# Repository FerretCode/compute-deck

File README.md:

# Compute Deck

**Compute Deck** is an open-source portable Linux computer and cyberdeck platform. It features a BlackBerry Q10 physical keyboard, dedicated power management with LiPo charging, an RP2040 coprocessor serving as an I2C keyboard bridge, and a Linux compute module.

> [!WARNING]
> ### ⚠️ Hardware Revision Notice: RK3566 Migration In Progress
>
> Revisions 1 and 2 of this project were built and verified around a **Raspberry Pi Zero / Zero 2 W** form-factor header.
>
> The project is currently undergoing a major hardware architecture update to migrate from the Pi Zero header to an integrated Rockchip RK3566 SoC directly on the board.
---

## Project Overview & Key Features

- **Physical Keyboard Integration:** Uses a BlackBerry Q10 keyboard connected using a 24-pin Hirose BM14B connector.
- **Dedicated RP2040 Coprocessor:** Offloads the keyboard control from the processor, supporting debouncing, key remapping, and layer management.
- **I2C Slave Keyboard Bridge:** Communicates with the host system via I2C at address `0x1F`, sending keycodes to the main processor.
- **Power Management Subsystem:** Integrated IP5306 power bank SoC managing single-cell LiPo battery charging, 5V boost conversion, power routing, status LEDs, and soft-latching power control alongside an AMS1117-3.3 regulator.
- **Linux Host Virtual Keyboard Driver:** Python user-space daemon using Linux `/dev/uinput` and `evdev` to translate the RP2040 I2C keycodes into full USB keyboard input with support for modifiers.

---

## Repository Structure

```
compute-deck/
├── firmware/                   # RP2040 Coprocessor Firmware (Pico SDK C/C++)
│   ├── CMakeLists.txt          # CMake build configuration
│   ├── main.c                  # Keyboard matrix scanner, layer logic & I2C slave handler
├── hardware/                   # KiCad PCB & Schematic Design Files
│   ├── footprints/             # Custom KiCad component footprints
│   ├── symbols/                # Custom KiCad schematic symbols
├── host/                       # Host Linux Software & Services
│   ├── keyboard_driver.py      # Python I2C polling daemon & uinput event injector
│   ├── q10-keyboard.service    # Systemd service unit for boot startup
```

---

## RP2040 Firmware Setup

### Build Prerequisites

- [Raspberry Pi Pico SDK](https://github.com/raspberrypi/pico-sdk) configured in your environment (`PICO_SDK_PATH`).
- `cmake`
- GCC ARM Cross-compiler (`arm-none-eabi-gcc`)

### Building the Firmware

```bash
cd firmware
mkdir build
cd build
cmake ..
make -j$(nproc)
```

### Flashing

1. Short the `BOOTSEL` jumper on the board using tweezers or other conductive object while plugging in USB to enter the RP2040 into bootloader mode.
2. Drag and drop `q10_keyboard.uf2` onto the mounted `RPI-RP2` USB storage drive.

---

## Host Driver Setup (Linux / Raspberry Pi OS)

The host driver in `host/` runs on the Linux compute host (e.g. Raspberry Pi OS or Linux kernel with `/dev/uinput` enabled).

### 1. Enable I2C Interface
Enable the hardware I2C interface on the host SBC:

```bash
sudo raspi-config nonint do_i2c 0
```

### 2. Install Dependencies
```bash
sudo apt-get install python3-pip python3-smbus
pip3 install -r host/requirements.txt
```

### 3. Grant Permissions

Add your user to the `i2c` and `input` groups:

```bash
sudo usermod -aG i2c,input $USER
```

### 4. Running the Driver

Run the driver manually to verify key injection:

```bash
python3 host/keyboard_driver.py
```

### 5. Install as a Systemd Daemon

To launch the keyboard driver automatically at boot:

```bash
sudo mkdir -p /opt/q10-keyboard
sudo cp host/keyboard_driver.py /opt/q10-keyboard/
sudo cp host/q10-keyboard.service /etc/systemd/system/
sudo systemctl daemon-reload
sudo systemctl enable --now q10-keyboard.service
```

---

## Keyboard Layout & Modifier Behavior

The physical layout follows the BlackBerry Q10 matrix mapping:

- **Shift:** One-shot modifier. Pressing Shift capitalizes the next key typed, and then automatically clears.
- **Alt:** Accesses numbers and secondary symbols printed on keycaps (e.g., Q -> `#`, W -> `1`, E -> `2`).
- **Sym:** Accesses extended navigation and punctuation symbols (e.g., Q -> `Esc`, W -> `Up`, A -> `Left`, S -> `Down`, D -> `Right`, T -> `Tab`).
- **Mic Key:** Mapped as Super. Supports tap-or-chord timeout (`0.4s`).
- **Ctrl:** Left Control key with chord support.

---

## Fabrication & Manufacturing

Production files generated for JLCPCB are stored under `hardware/production/`

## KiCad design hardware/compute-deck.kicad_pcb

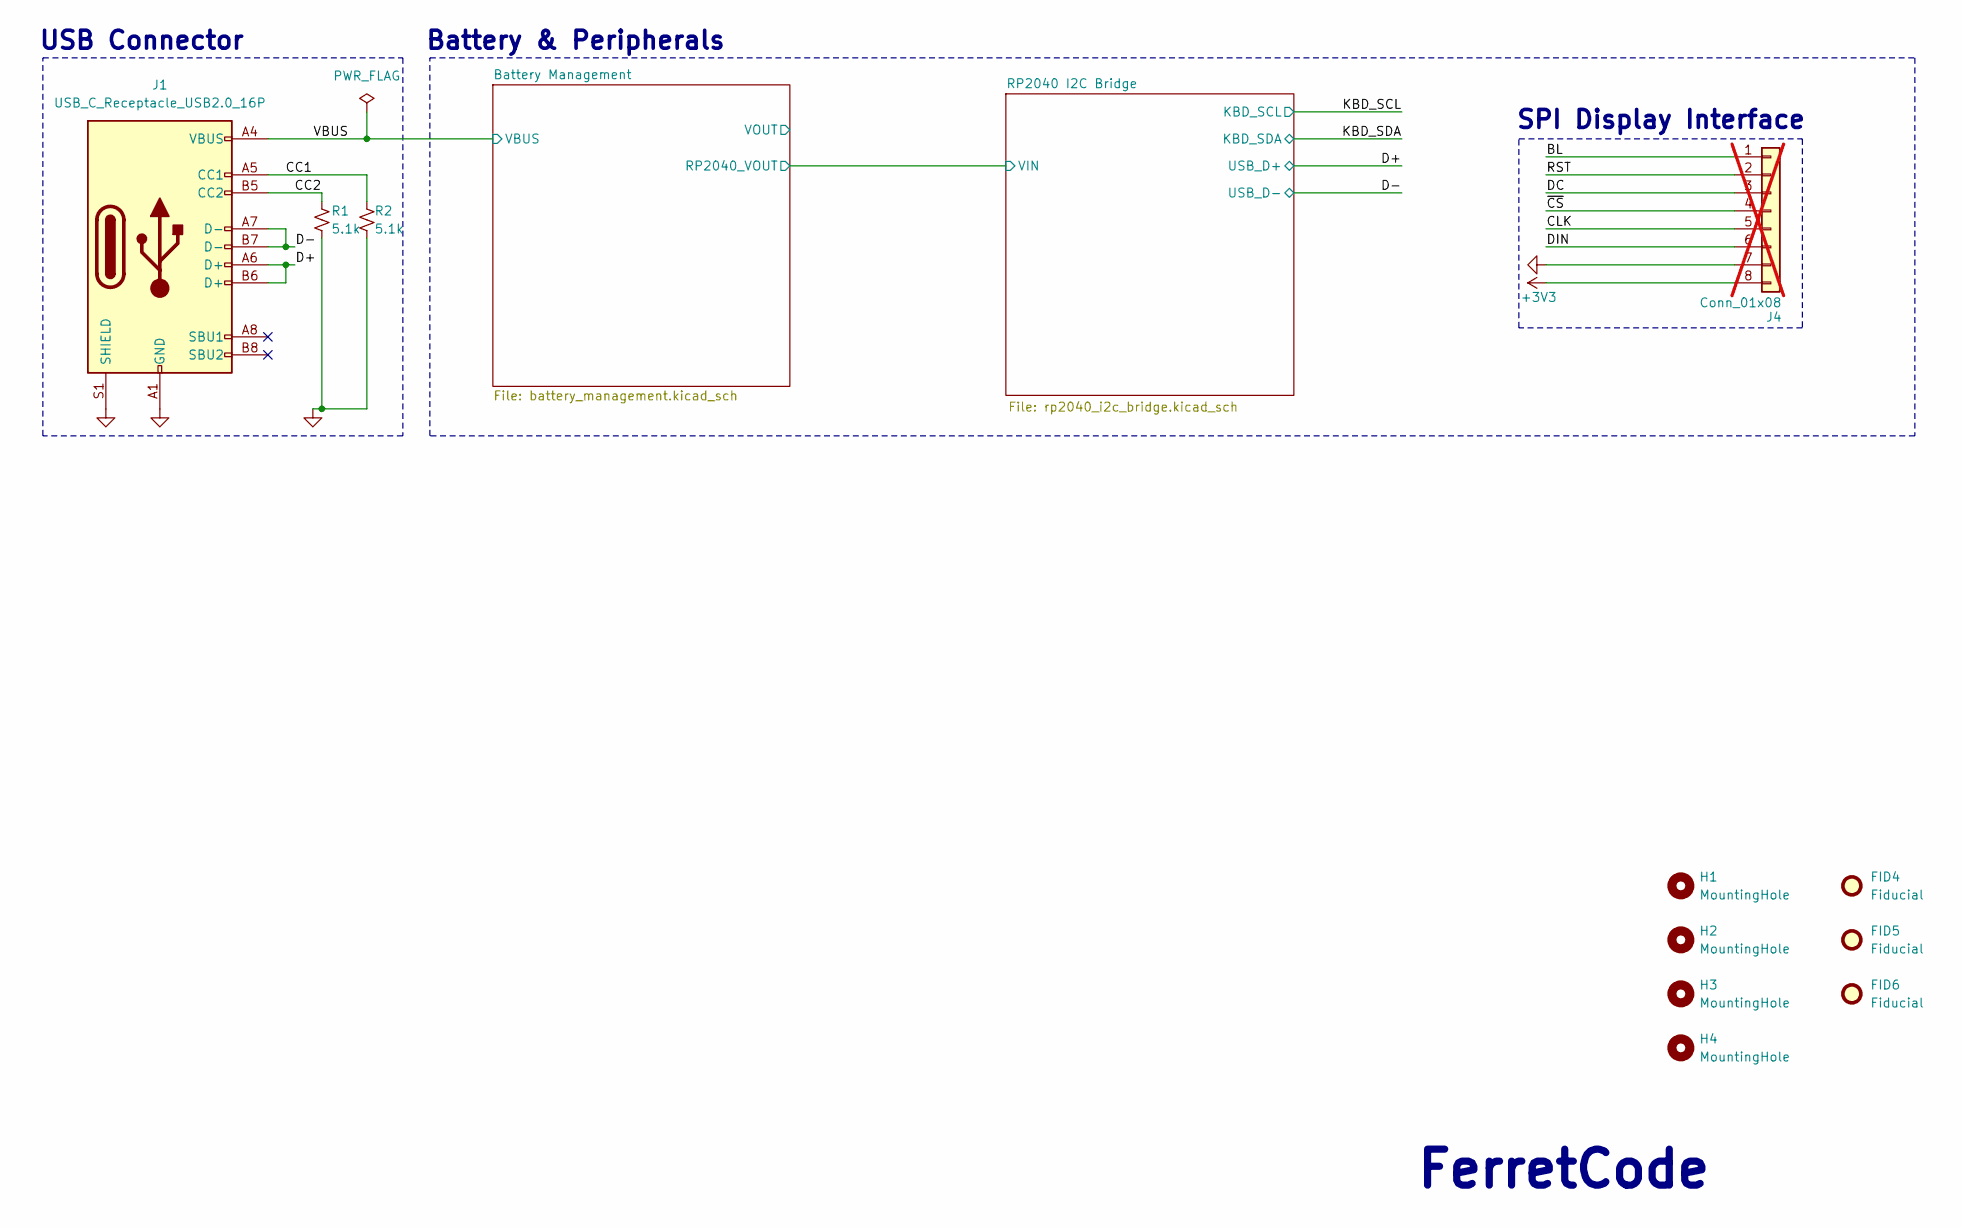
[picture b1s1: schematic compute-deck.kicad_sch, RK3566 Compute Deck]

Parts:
FID4, FID5, FID6: Fiducial; Fiducial_1mm_Mask3mm
H1, H2, H3, H4: MountingHole; MountingHole_2.7mm_M2.5
J1: USB_C_Receptacle_USB2.0_16P; USB_C_Receptacle_HRO_TYPE-C-31-M-12; LCSC PN C165948
J4: Conn_01x08; PinHeader_1x08_P2.54mm_Vertical; not fitted
R1, R2: 5.1k; R_0402_1005Metric; LCSC PN C23186

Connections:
+3V3: J4.8; also elsewhere on the board
/BL: J4.1; also elsewhere on the board
/CC1: J1.A5 (CC1), R2.1
/CC2: J1.B5 (CC2), R1.1
/CLK: J4.5; also elsewhere on the board
/D+: J1.A6 (D+), J1.B6 (D+); also elsewhere on the board
/D-: J1.A7 (D-), J1.B7 (D-); also elsewhere on the board
/DC: J4.3; also elsewhere on the board
/DIN: J4.6; also elsewhere on the board
/RST: J4.2; also elsewhere on the board
/VBUS: J1.A4 (VBUS), J1.A9 (VBUS), J1.B4 (VBUS), J1.B9 (VBUS); also elsewhere on the board
/~CS: J4.4; also elsewhere on the board
GND: J1.A1 (GND), J1.A12 (GND), J1.B1 (GND), J1.B12 (GND), J1.S1 (SHIELD), J4.7, R1.2, R2.2; also elsewhere on the board

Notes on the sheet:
Battery & Peripherals
FerretCode
SPI Display Interface
USB Connector

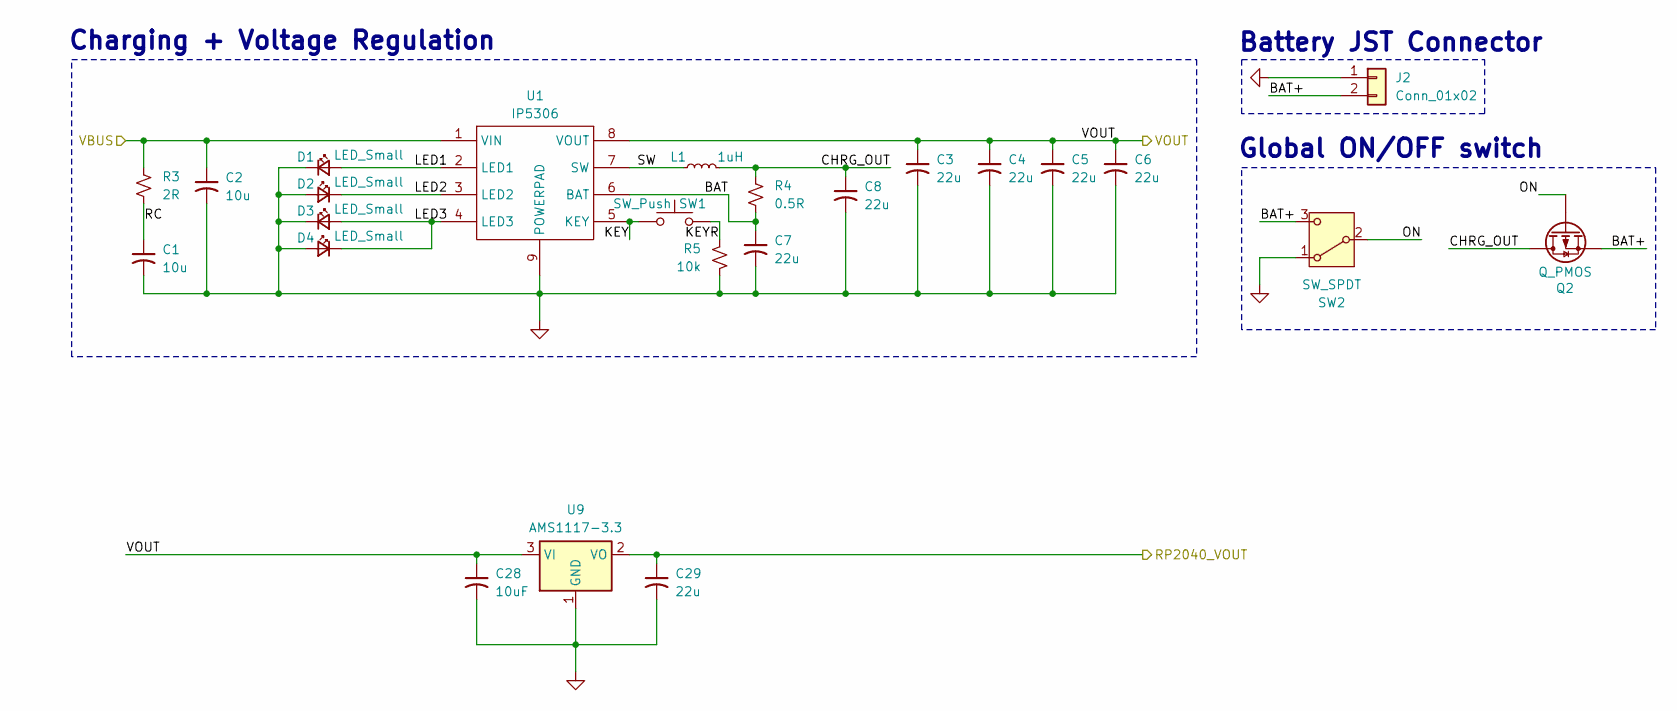
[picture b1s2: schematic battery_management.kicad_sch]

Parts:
C1, C2: 10u; C_0603_1608Metric; LCSC PN C19702
C3, C4, C5, C6: 22u; C_0805_2012Metric; LCSC PN C29277
C7: 22u; C_0402_1005Metric; LCSC PN C60077
C8: 22u; C_0603_1608Metric; LCSC PN C60077
C28: 10uF; C_0603_1608Metric; LCSC C19702
C29: 22u; C_0603_1608Metric; LCSC C59461
D1, D2, D3, D4: LED_Small; LED_0603_1608Metric; LCSC PN C6695603
J2: Conn_01x02; JST_PH_S2B-PH-K_1x02_P2.00mm_Horizontal; LCSC PN C157932
L1: 1uH; L_Taiyo-Yuden_NR-60xx; LCSC PN C2903082
Q2: Q_PMOS; SOT-23
R3: 2R; R_0603_1608Metric; LCSC PN C22977
R4: 0.5R; R_0402_1005Metric; LCSC PN C45312
R5: 10k; R_0402_1005Metric; LCSC PN C25804
SW1: SW_Push; SW_Push_1P1T_NO_CK_KMR2; LCSC PN C221675
SW2: SW_SPDT; SW_SPDT_PCM12
U1: IP5306; SOP127P600X165-9N
U9: AMS1117-3.3; SOT-223-3_TabPin2; LCSC C6186

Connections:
/BAT: C7.1, R4.2, U1.6 (BAT)
/BAT+: J2.2, Q2.S, SW2.3 (C)
/CHRG_OUT: C8.1, L1.2, Q2.D, R4.1
/KEY: SW1.1, U1.5 (KEY)
/KEYR: R5.1, SW1.2
/LED1: D1.2 (A), U1.2 (LED1)
/LED2: D2.1 (K), U1.3 (LED2)
/LED3: D3.2 (A), D4.1 (K), U1.4 (LED3)
/ON: Q2.G, SW2.2 (B)
/RC: C1.1, R3.2
/SW: L1.1, U1.7 (SW)
/VBUS: C2.1, R3.1, U1.1 (VIN); also elsewhere on the board
/VOUT: C3.1, C4.1, C5.1, C6.1, C28.1, U1.8 (VOUT), U9.3 (VI); also elsewhere on the board
GND: C1.2, C2.2, C3.2, C4.2, C5.2, C6.2, C7.2, C8.2, C28.2, C29.2, D1.1 (K), D2.2 (A), D3.1 (K), D4.2 (A), J2.1, R5.2, SW2.1 (A), U1.9 (POWERPAD), U9.1 (GND); also elsewhere on the board
unnamed: C29.1, U9.2 (VO)

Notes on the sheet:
Charging + Voltage Regulation
Global ON/OFF switch
Battery JST Connector

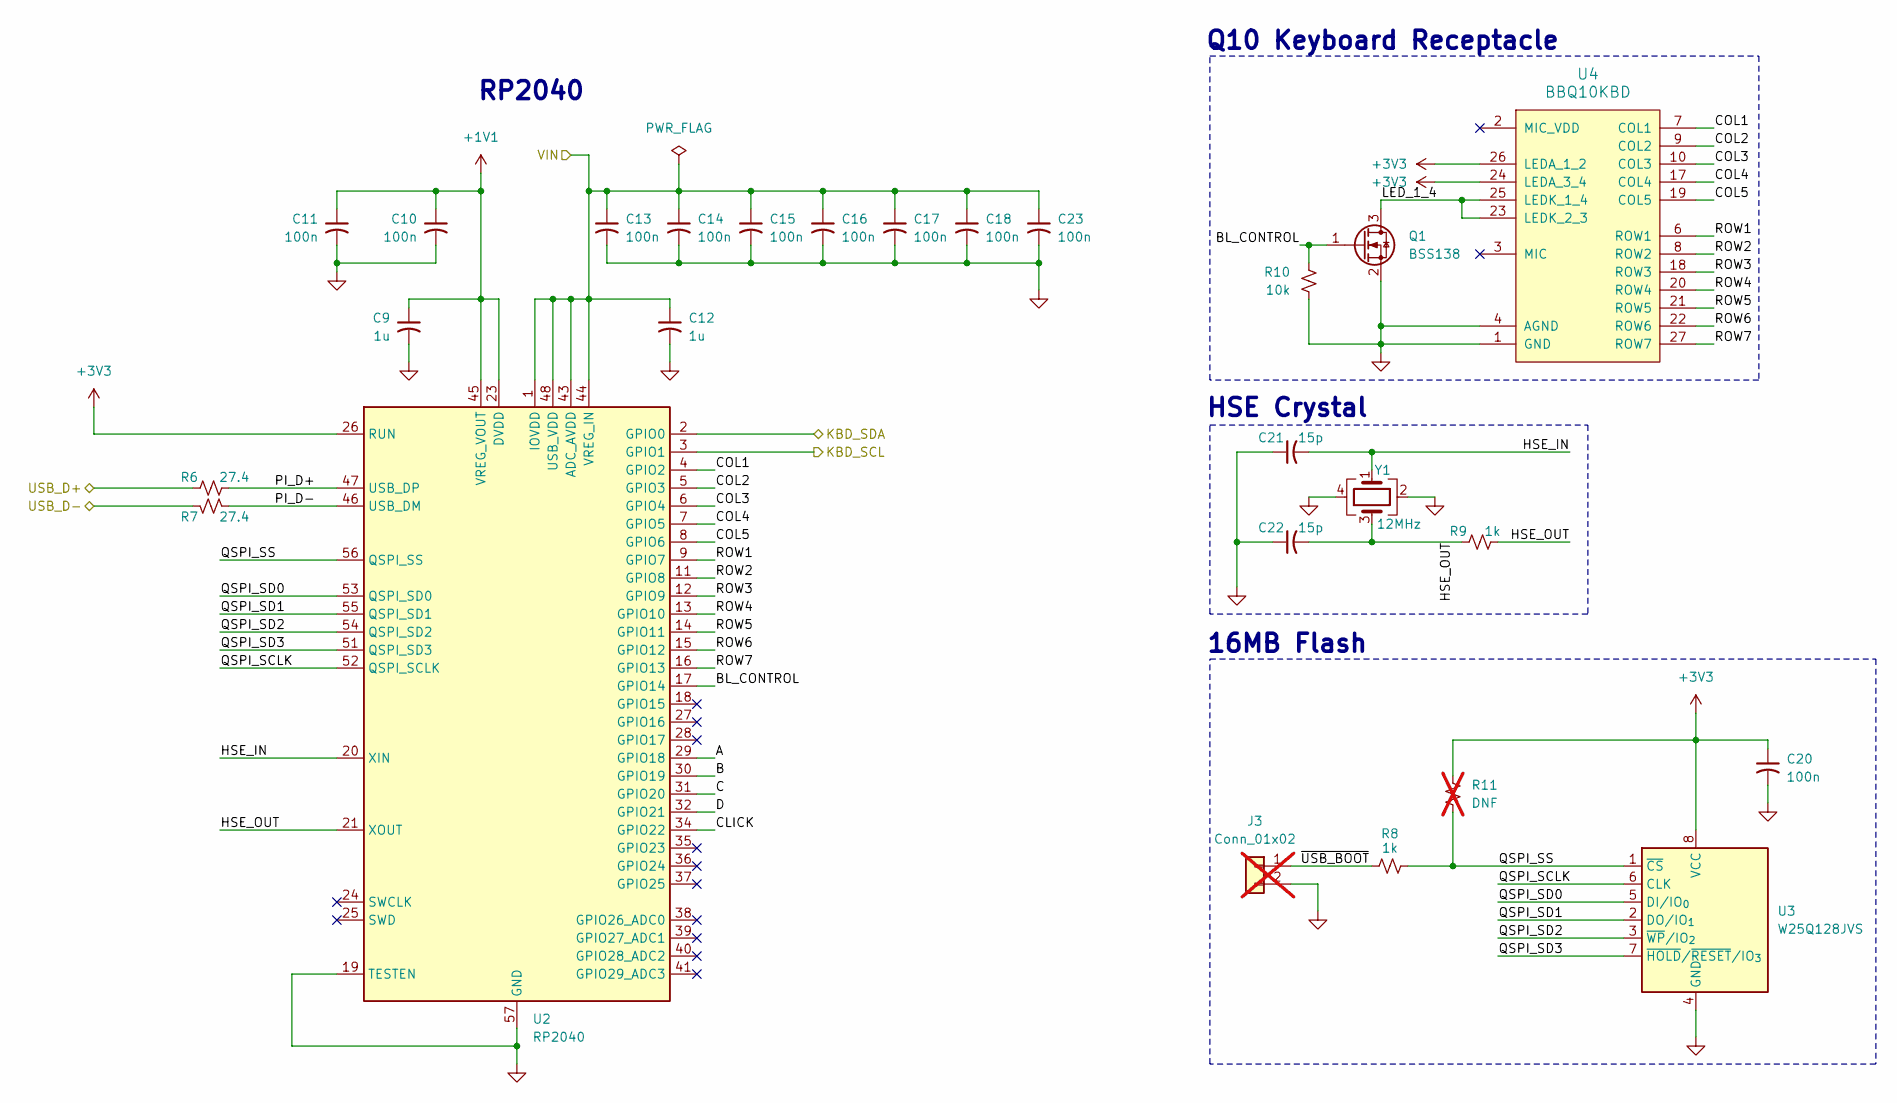
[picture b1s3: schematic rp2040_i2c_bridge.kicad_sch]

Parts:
C9: 1u; C_0402_1005Metric; LCSC PN C14445
C10, C11, C13, C14, C16, C17, C18: 100n; C_0402_1005Metric; LCSC PN C71687
C12: 1u; C_0603_1608Metric; LCSC PN C14445
C15: 100n; C_0402_1005Metric
C20: 100n; C_0603_1608Metric; LCSC PN C1590
C21, C22: 15p; C_0402_1005Metric; LCSC PN C1548
C23: 100n; C_0402_1005Metric_Pad0.74x0.62mm_HandSolder; LCSC PN C71687
J3: Conn_01x02; PinHeader_1x02_P2.54mm_Vertical; not fitted
Q1: BSS138; SOT-23; LCSC PN C52895
R6, R7: 27.4; R_0402_1005Metric; LCSC PN C177713
R8, R9: 1k; R_0402_1005Metric; LCSC PN C21190
R10: 10k; R_0603_1608Metric; LCSC PN C25804
R11: DNF; R_0402_1005Metric; not fitted
U2: RP2040; QFN-56-1EP_7x7mm_P0.4mm_EP3.2x3.2mm; LCSC PN C2040
U3: W25Q128JVS; SOIC-8_5.3x5.3mm_P1.27mm
U4: BBQ10KBD; BM14B(0.8)-24DS-0.4V(53)
Y1: 12MHz; Crystal_SMD_3225-4Pin_3.2x2.5mm; LCSC PN C9002

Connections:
+1V1: C9.1, C10.1, C11.1, U2.23 (DVDD), U2.45 (VREG_VOUT), U2.50 (DVDD)
+3V3: C12.1, C13.1, C14.1, C15.1, C16.1, C17.1, C18.1, C20.1, C23.1, R11.1, U2.1 (IOVDD), U2.10 (IOVDD), U2.22 (IOVDD), U2.26 (RUN), U2.33 (IOVDD), U2.42 (IOVDD), U2.43 (ADC_AVDD), U2.44 (VREG_IN), U2.48 (USB_VDD), U2.49 (IOVDD), U3.8 (VCC), U4.24 (LEDA_3_4), U4.26 (LEDA_1_2); also elsewhere on the board
/D+: R6.1; also elsewhere on the board
/D-: R7.1; also elsewhere on the board
/KBD_SCL: U2.3 (GPIO1); also elsewhere on the board
/KBD_SDA: U2.2 (GPIO0); also elsewhere on the board
/RP2040 I2C Bridge/A: U2.29 (GPIO18)
/RP2040 I2C Bridge/B: U2.30 (GPIO19)
/RP2040 I2C Bridge/BL_CONTROL: Q1.1 (G), R10.1, U2.17 (GPIO14)
/RP2040 I2C Bridge/C: U2.31 (GPIO20)
/RP2040 I2C Bridge/CLICK: U2.34 (GPIO22)
/RP2040 I2C Bridge/COL1: U2.4 (GPIO2), U4.7 (COL1)
/RP2040 I2C Bridge/COL2: U2.5 (GPIO3), U4.9 (COL2)
/RP2040 I2C Bridge/COL3: U2.6 (GPIO4), U4.10 (COL3)
/RP2040 I2C Bridge/COL4: U2.7 (GPIO5), U4.17 (COL4)
/RP2040 I2C Bridge/COL5: U2.8 (GPIO6), U4.19 (COL5)
/RP2040 I2C Bridge/D: U2.32 (GPIO21)
/RP2040 I2C Bridge/HSE_IN: C21.2, U2.20 (XIN), Y1.1
/RP2040 I2C Bridge/HSE_OUT: C22.2, R9.1, R9.2, U2.21 (XOUT), Y1.3
/RP2040 I2C Bridge/LED_1_4: Q1.3 (D), U4.23 (LEDK_2_3), U4.25 (LEDK_1_4)
/RP2040 I2C Bridge/PI_D+: R6.2, U2.47 (USB_DP)
/RP2040 I2C Bridge/PI_D-: R7.2, U2.46 (USB_DM)
/RP2040 I2C Bridge/QSPI_SCLK: U2.52 (QSPI_SCLK), U3.6 (CLK)
/RP2040 I2C Bridge/QSPI_SD0: U2.53 (QSPI_SD0), U3.5 (DI/IO_{0})
/RP2040 I2C Bridge/QSPI_SD1: U2.55 (QSPI_SD1), U3.2 (DO/IO_{1})
/RP2040 I2C Bridge/QSPI_SD2: U2.54 (QSPI_SD2), U3.3 (~WP/IO_{2})
/RP2040 I2C Bridge/QSPI_SD3: U2.51 (QSPI_SD3), U3.7 (~HOLD/~RESET/IO_{3})
/RP2040 I2C Bridge/QSPI_SS: R8.2, R11.2, U2.56 (QSPI_SS), U3.1 (~CS)
/RP2040 I2C Bridge/ROW1: U2.9 (GPIO7), U4.6 (ROW1)
/RP2040 I2C Bridge/ROW2: U2.11 (GPIO8), U4.8 (ROW2)
/RP2040 I2C Bridge/ROW3: U2.12 (GPIO9), U4.18 (ROW3)
/RP2040 I2C Bridge/ROW4: U2.13 (GPIO10), U4.20 (ROW4)
/RP2040 I2C Bridge/ROW5: U2.14 (GPIO11), U4.21 (ROW5)
/RP2040 I2C Bridge/ROW6: U2.15 (GPIO12), U4.22 (ROW6)
/RP2040 I2C Bridge/ROW7: U2.16 (GPIO13), U4.27 (ROW7)
/RP2040 I2C Bridge/~USB_BOOT: J3.1, R8.1
GND: C9.2, C10.2, C11.2, C12.2, C13.2, C14.2, C15.2, C16.2, C17.2, C18.2, C20.2, C21.1, C22.1, C23.2, J3.2, Q1.2 (S), R10.2, U2.19 (TESTEN), U2.57 (GND), U3.4 (GND), U4.1 (GND), U4.4 (AGND), U4.5 (GND), U4.11 (GND), U4.12 (GND), U4.13 (GND), U4.14 (GND), U4.15 (GND), U4.16 (GND), U4.28 (GND), Y1.2, Y1.4; also elsewhere on the board

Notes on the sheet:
Q10 Keyboard Receptacle
RP2040
16MB Flash
HSE Crystal

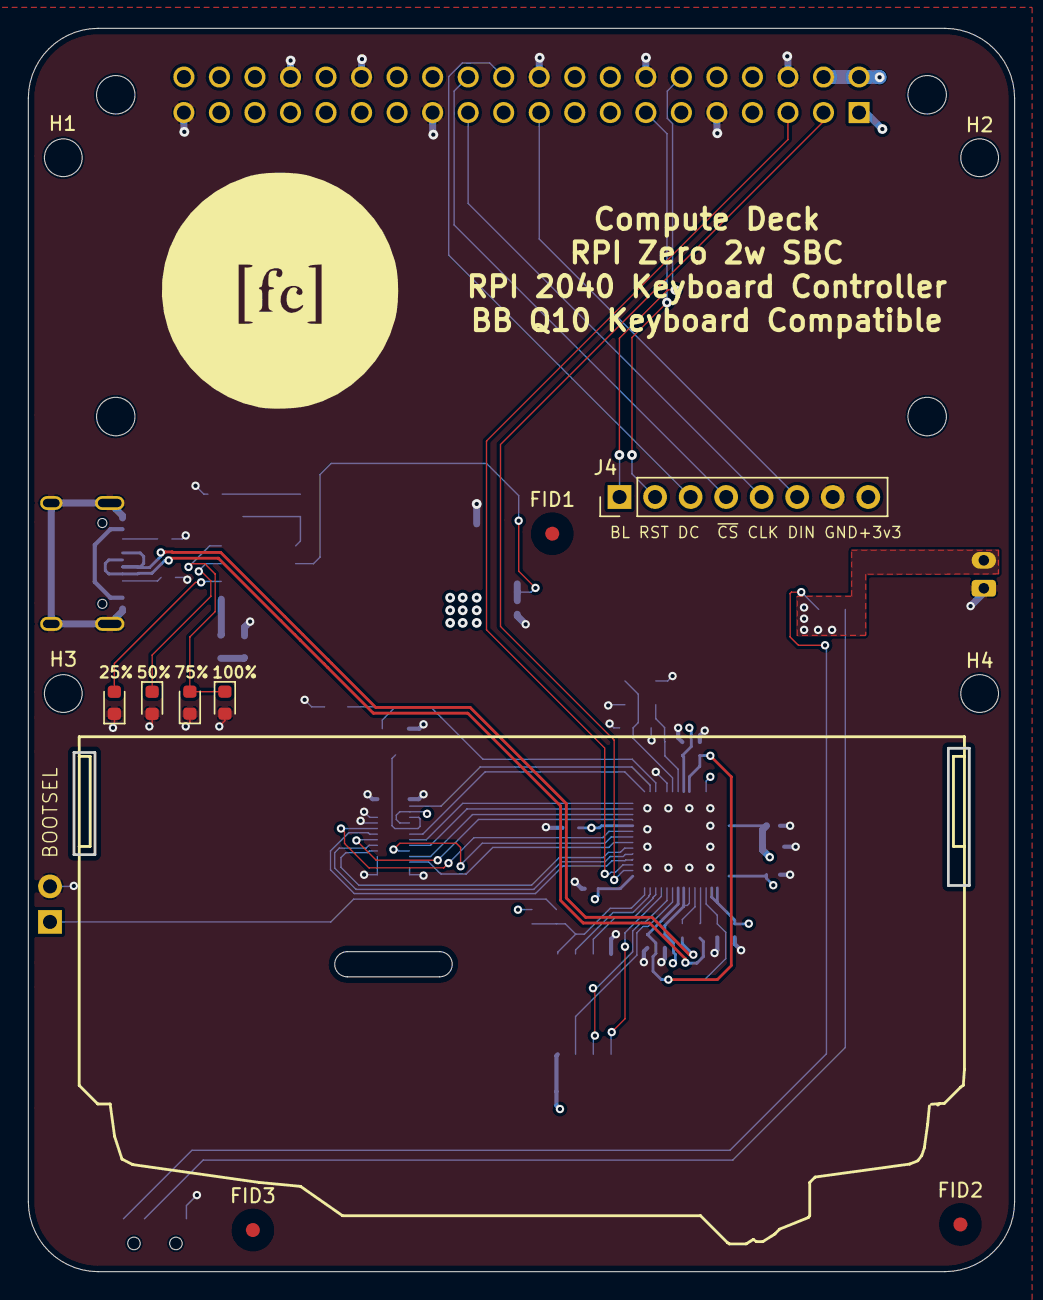
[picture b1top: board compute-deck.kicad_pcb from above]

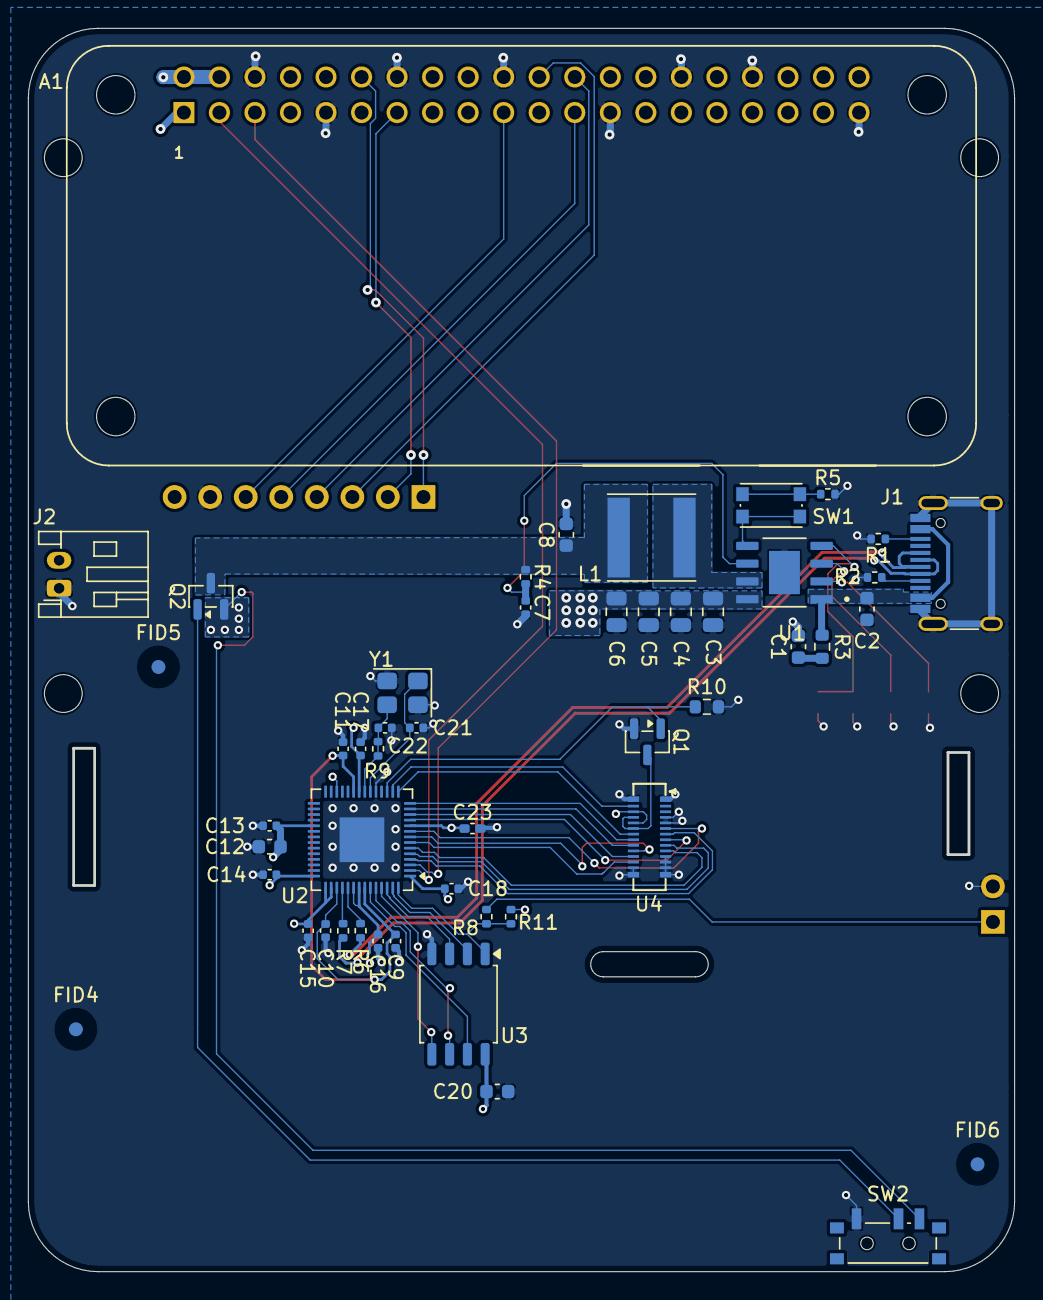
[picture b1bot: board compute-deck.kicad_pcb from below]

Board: 4 copper layers, 70.4 x 88.7 mm, 62 parts (50 on the bottom side), 53 nets.

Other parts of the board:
A1: RASPBERRYPI-ZERO; RASPBERRYPI-ZERO_RPI-ZERO
FID1, FID2, FID3: Fiducial; Fiducial_1mm_Mask3mm

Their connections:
+3V3: A1.1 (3V3[1]); also elsewhere on the board
/BL: A1.12 (GPIO18); also elsewhere on the board
/CLK: A1.23 (GPIO11/SCLK); also elsewhere on the board
/DC: A1.22 (GEN/6GPIO25); also elsewhere on the board
/DIN: A1.19 (GPIO10/MOSI); also elsewhere on the board
/KBD_SCL: A1.5 (GPIO3/SCL); also elsewhere on the board
/KBD_SDA: A1.3 (GPIO2/SDA); also elsewhere on the board
/RST: A1.13 (GPIO27/GEN2); also elsewhere on the board
/VOUT: A1.2 (5V[1]), A1.4 (5V[2]); also elsewhere on the board
/~CS: A1.24 (~CE0/GPIO8); also elsewhere on the board
GND: A1.6 (GND[8]), A1.9 (GND[1]), A1.14 (GND[4]), A1.20 (GND[5]), A1.25 (GND[2]), A1.30 (GND[6]), A1.34 (GND[7]), A1.39 (GND[3]); also elsewhere on the board

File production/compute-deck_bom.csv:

Designator,Footprint,Quantity,Value,LCSC Part #
A1,RASPBERRYPI-ZERO_RPI-ZERO,1,RASPBERRYPI-ZERO,
"C1, C2",0603,2,10u,C19702
"C10, C11, C13, C14, C16, C17, C18, C23",0402,8,100n,C71687
C12,0603,1,1u,C14445
C15,0402,1,100n,
C20,0603,1,100n,C1590
"C21, C22",0402,2,15p,C1548
"C3, C4, C5, C6",0805,4,22u,C29277
C7,0402,1,22u,C60077
C8,0603,1,22u,C60077
C9,0402,1,1u,C14445
"D1, D2, D3, D4",0603,4,LED_Small,C6695603
J1,USB_C_Receptacle_HRO_TYPE-C-31-M-12,1,USB_C_Receptacle_USB2.0_16P,C165948
J2,JST_PH_S2B-PH-K_1x02_P2.00mm_Horizontal,1,Conn_01x02,C157932
L1,L_Taiyo-Yuden_NR-60xx,1,1uH,C2903082
Q1,SOT-23,1,BSS138,C52895
Q2,SOT-23,1,Q_PMOS,
"R1, R2",0402,2,5.1k,C23186
R10,0603,1,10k,C25804
R3,0603,1,2R,C22977
R4,0402,1,0.5R,C45312
R5,0402,1,10k,C25804
"R6, R7",0402,2,27.4,C177713
"R8, R9",0402,2,1k,C21190
SW1,SW_Push_1P1T_NO_CK_KMR2,1,SW_Push,C221675
SW2,SW_SPDT_PCM12,1,SW_SPDT,
U1,SOP127P600X165-9N,1,IP5306,
U2,QFN-56-1EP_7x7mm_P0.4mm_EP3.2x3.2mm,1,RP2040,C2040
U3,SOIC-8_5.3x5.3mm_P1.27mm,1,W25Q128JVS,
U4,BM14B(0.8)-24DS-0.4V(53),1,BBQ10KBD,
Y1,Crystal_SMD_3225-4Pin_3.2x2.5mm,1,12MHz,C9002

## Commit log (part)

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2025-12-24 add compute deck
2025-12-25 add pdf
